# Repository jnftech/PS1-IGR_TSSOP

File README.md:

## Playstation 1 In-Game Reset (IGR)
### QSBs for One-wire Controller-PCB installs
<br/>
<br/>

These boards are variations on [PyroESP's](https://github.com/pyroesp) Playstation 1 Reset Mod project.

The original project and code can be found at https://github.com/pyroesp/PlayStation-1-Reset-Mod

To simplify the goal of this project: When installed into a Playstation 1 system, it facilitates a reset of the system using a button combination on controller 1, by tapping into the controller signals and toggling the system reset line. This is useful for those that have ODEs installed, as you can reset back to the menu of the ODE from the controller instead of getting up to hold the reset button down.

Originally I had posted a variation that was more or less a shrink of their original PCB (which used a SOIC package for the microcontroller), instead using the TSSOP version - to get the board as small as it could be for S&Gs and more of a "hardmode" install. This version of the project (while deprecated, unless you REALLY need to avoid installing to the controller PCB) is still hosted in the repository.

A while back (2002? Yes it has taken me that long to publish the final versions here) a member of the [Consolemods.org](https://www.consolemods.org) discord observed a variation on OSHpark that installed to the back of the controller PCB behind the player 1 port. However the project was not laid out correctly, thus the wrong (higher) voltage was applied to the microcontroller. This style of board is a "Quick Solder Board" (QSB), where the board is designed to sit on top of another PCB and solder directly to signal points (versus running a wire for each signal). Such a solution allows for a "one-wire" install of this project. All but one of the signals needed are available from the solder points of the controller ports themselves. The only wire that must be run is for the reset signal.
While these controller-PCB-mounted solutions were not uncommon at the time, the project on OSHpark appeared to the only published gerbers for folks that prefer to fabricate their own PCBs.
I decided to revisit the project to produce a correctly-wired version, using my own consoles for measurement. Some earlier versions of the gerbers were posted to the discord for members to use. This respository has three variations depending on your soldering preferences.
  
Code, details of the solution, original PCB design, and instructions for programming and installation are available at [pyroesp's Github](https://github.com/pyroesp). Programming-ready hex file in the [releases section](https://github.com/pyroesp/PlayStation-1-Reset-Mod/releases)

### Controller-port (Port 1) install, SOIC Package (Normal difficulty) [(OSHpark)](https://oshpark.com/shared_projects/fwJTyytg)

This variant more or less aimed to substitute the faulty one on OSHpark. Installs over the solder points for controller port 1 and uses the SOIC package of the microcontroller (MCU). This should be fairly easy to assemble for anyone with decent soldering skills.

### Controller-port (Port 1) install, TSSOP Package (Hard difficulty) [(OSHpark)](https://oshpark.com/shared_projects/G71d1amG)

This is almost identical to the above variant, and installs the exact same way. The only difference is the use of the TSSOP package for the MCU. This requires slightly tighter soldering skills.

### Controller-ribbon connector (Center of controller PCB) install, UQFN Package (Ultrahard difficulty) [(OSHpark)](https://oshpark.com/shared_projects/B2ZQAGCg)

Staying in the same spirit as my original visit to the project, this board aims to be as small is it can be. I realized that another spot on the controller PCB contained all the same signals as the controller port: The connector for the ribbon cable that connects the controller assembly to the main system board. This PCB installs to the back of that connector instead of the controller port. Continuing with that same spirit, I figured go all out and use the UQFN package of the MCU - which is the smallest package it comes in. However this means this board is significantly more difficult to assemble by hand. Not impossible - I hand assembled the one installed in my main console - but takes very good soldering skills and tools. I imagine this is the smallest "one-wire" install of this solution available. All that said, the actual installation of the board into the console should not be much more difficult than the other two options.

### BOM:

Only two components are needed:

**U1**<br/> Depending on which board you which to assemble, the part number for the MCU will differ slightly (only the last two characters of the part number matter in this case)
- SOIC: Microchip PIC16F18325-I/SL. [Digikey](https://www.digikey.com/en/products/detail/microchip-technology/PIC16F18325-I-SL/5323625)
- TSSOP: Microchip PIC16F18325-I/ST. [Digikey](https://www.digikey.com/en/products/detail/microchip-technology/PIC16F18325-I-ST/5323626)
- UQFN: Microchip PIC16F18325-I/JQ. [Digikey](https://www.digikey.com/en/products/detail/microchip-technology/PIC16F18325-I-JQ/5639473)

**C1**:<br/>You really don't need to be picky about this part. Any 100nf to 1000nf/1uf 0603-sized Ceramic capacitor rated at 16v or above will work. <br />
    Examples:<br />
        [Samsung CL10B104KB8NNNL](https://www.digikey.com/en/products/detail/samsung-electro-mechanics/CL10B104KB8NNNL/3894274)<br />
        [Murata GCJ188R71E104KA12D](https://www.digikey.com/en/products/detail/murata-electronics/GCJ188R71E104KA12D/7363221)

### Notes:
- These have not been designed with the PSone in mind, and are only tested on the original "phat" models. While the PSones have no good ODE option (where this mod is most useful), I may take a quick look the next time I have a PSone open (maybe requires another board revision). 
- There are other variants of the MCU you can use, depending on whether you have trouble sourcing the above (I did when I built my prototypes) but they may be a few cents more expensive as they have extra features or tolerances. In this project, they will all function identically:
  - The "I/" in the part number can be swapped with the "E/" variant. The latter is just "Extended Tempurature range"
  - This project uses the PIC16F18325 MCU, however the the PIC16F18**326** can also be used. It's the exact same MCU with a little bit more memory and storage. Same HEX file can be used to program either. The board I installed in my main console uses the PIC16F18326-E/JQ part. While the size of the code is fairly small, the next MCU down in the list (324) CANNOT be used as it lacks the dual SPI capability of the 325 and 326 (which this project requires).
- You will of course need a programmer to flash the code to the microcontroller, such as a PICkit3. This can be done in several ways:
  - The ICSP pads on board by soldering some temporary wiring to connect it to the programmer.
  - The ICSP pads by using a 2mm pitch pogo-pin PCB clamp such as this one on [Aliexpress](https://www.aliexpress.com/i/3256806664884457.html)
  - An alternative would be a DIP socket adapter ([an example of such on Aliexpress](https://www.aliexpress.com/item/32868905130.html)) to house the chip for programming before it is soldered to the board.
- The text in the bottom copper layer *may* cause some fabs to complain about the size of the text. OSHpark doesnt have an issue (they seem to fab whatever you throw at them, regardless if it comes out well in the final product), but I have experienced cases in the past where JLCPCB will remove any text from the board that they deem too small.

### Tools used for this project:
- Tracespace View (SVG conversions of gerbers for the above images) https://tracespace.io/view/
- KiCad 8.0.6 https://www.kicad.org/
- GIMP for some of the image edits.

### To-do
- Post more detailed installation instructions
- Post or link to reset line points for various motherboard revisions.

### License:
This derivative work maintains the same source license as the original board and project:  
Attribution-ShareAlike 4.0 International. See license file for more info

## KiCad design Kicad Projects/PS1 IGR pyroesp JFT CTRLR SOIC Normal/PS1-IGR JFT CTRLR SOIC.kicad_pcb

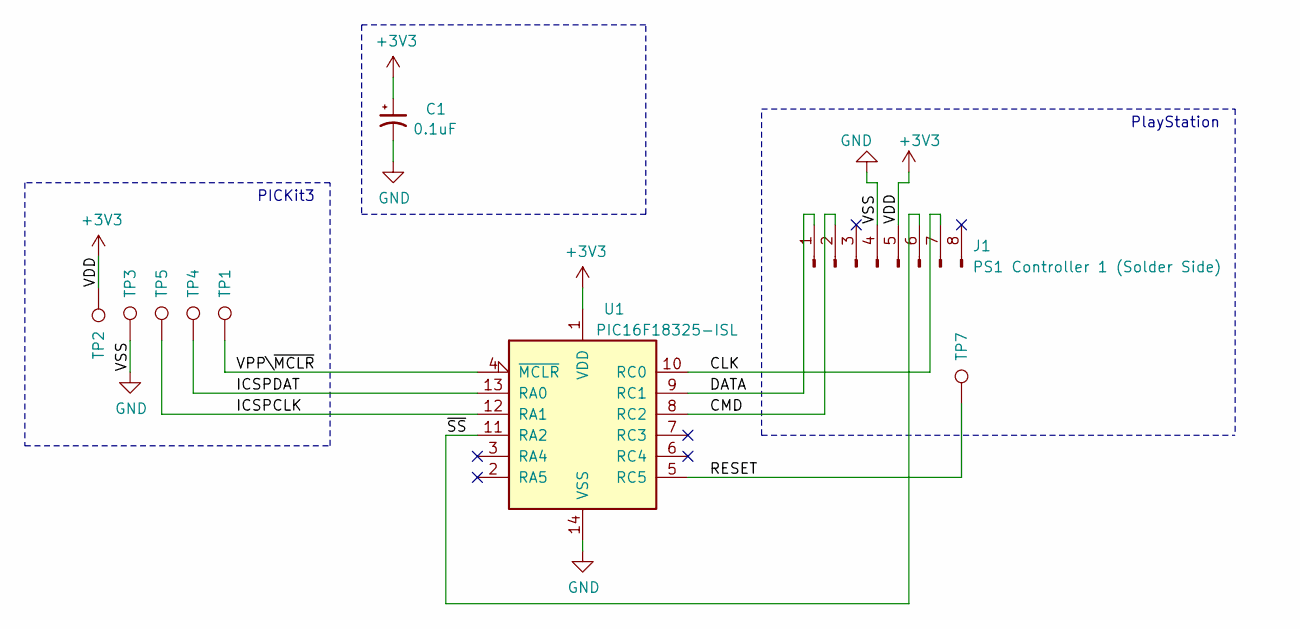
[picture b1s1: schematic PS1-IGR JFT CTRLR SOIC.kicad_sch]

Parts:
C1: 0.1uF; R_0603_0.8mm
J1: PS1 Controller 1 (Solder Side); PS1ControllerPort_SolderSide
TP1: VPP; TestPoint_Pad_NoSilk_D1.0mm
TP2: VDD; TestPoint_Pad_NoSilk_D1.0mm
TP3: VSS; TestPoint_Pad_NoSilk_D1.0mm
TP4: DAT; TestPoint_Pad_NoSilk_D1.0mm
TP5: CLK; TestPoint_Pad_NoSilk_D1.0mm
TP7: RST; Wirepad-2.54mm
U1: PIC16F18325-ISL; SOIC-14_3.9x8.7mm_Pitch1.27mm-JFT

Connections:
+3V3: C1.1, J1.5, TP2.1, U1.1 (VDD)
/CLK: J1.7, U1.10 (RC0)
/CMD: J1.2, U1.8 (RC2)
/DATA: J1.1, U1.9 (RC1)
/ICSPCLK: TP5.1, U1.12 (RA1)
/ICSPDAT: TP4.1, U1.13 (RA0)
/RESET: TP7.1, U1.5 (RC5)
/VPP\~MCLR: TP1.1, U1.4 (~MCLR)
/~SS: J1.6, U1.11 (RA2)
GND: C1.2, J1.4, TP3.1, U1.14 (VSS)

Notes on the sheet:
PICKit3
PlayStation

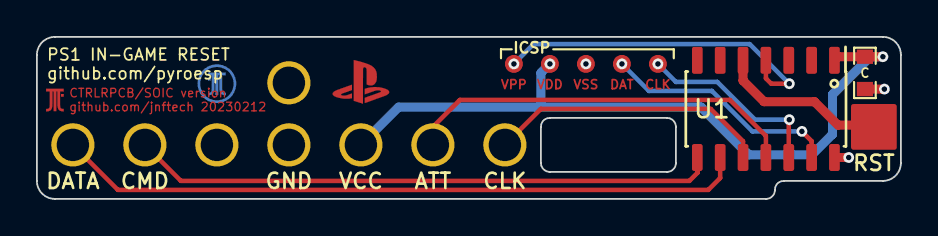
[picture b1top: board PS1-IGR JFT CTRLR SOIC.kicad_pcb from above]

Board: 2 copper layers, 48.0 x 9.0 mm, 9 parts (0 on the bottom side), 10 nets.

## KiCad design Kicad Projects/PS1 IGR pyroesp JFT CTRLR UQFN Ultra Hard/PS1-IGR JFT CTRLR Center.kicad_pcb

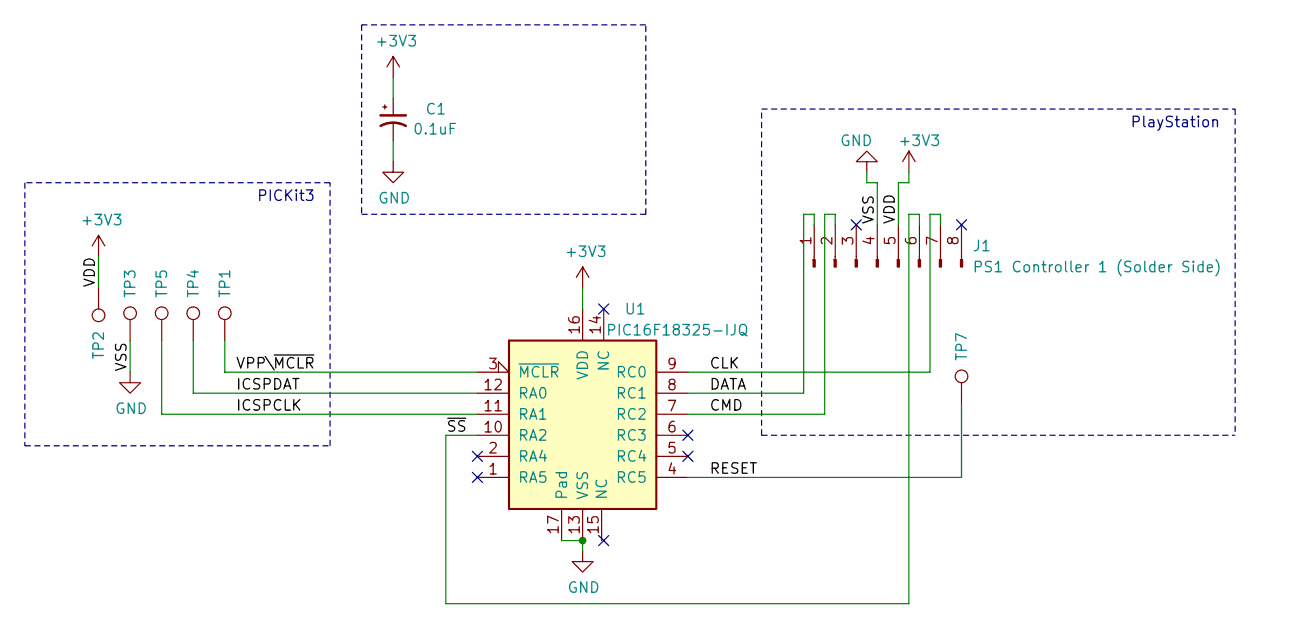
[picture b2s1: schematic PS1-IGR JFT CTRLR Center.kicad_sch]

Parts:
C1: 0.1uF; R_0603_0.8mm
J1: PS1 Controller 1 (Solder Side); PS1ctrlrRibbon_SolderSide_ForTHb
TP1: VPP; TestPoint_Pad_NoSilk_D1.0mm
TP2: VDD; TestPoint_Pad_NoSilk_D1.0mm
TP3: VSS; TestPoint_Pad_NoSilk_D1.0mm
TP4: DAT; TestPoint_Pad_NoSilk_D1.0mm
TP5: CLK; TestPoint_Pad_NoSilk_D1.0mm
TP7: RST; Wirepad-2x2.5mm
U1: PIC16F18325-IJQ; UQFN-16-1EP_4x4mm_P0.65mm_EP2.6x2.6mm

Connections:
+3V3: C1.1, J1.5, TP2.1, U1.16 (VDD)
/CLK: J1.7, U1.9 (RC0)
/CMD: J1.2, U1.7 (RC2)
/DATA: J1.1, U1.8 (RC1)
/ICSPCLK: TP5.1, U1.11 (RA1)
/ICSPDAT: TP4.1, U1.12 (RA0)
/RESET: TP7.1, U1.4 (RC5)
/VPP\~MCLR: TP1.1, U1.3 (~MCLR)
/~SS: J1.6, U1.10 (RA2)
GND: C1.2, J1.4, TP3.1, U1.13 (VSS), U1.17 (Pad)

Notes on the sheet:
PlayStation
PICKit3

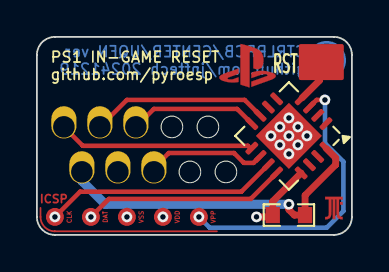
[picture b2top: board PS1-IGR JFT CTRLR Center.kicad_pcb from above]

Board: 2 copper layers, 17.5 x 11.0 mm, 9 parts (0 on the bottom side), 10 nets.

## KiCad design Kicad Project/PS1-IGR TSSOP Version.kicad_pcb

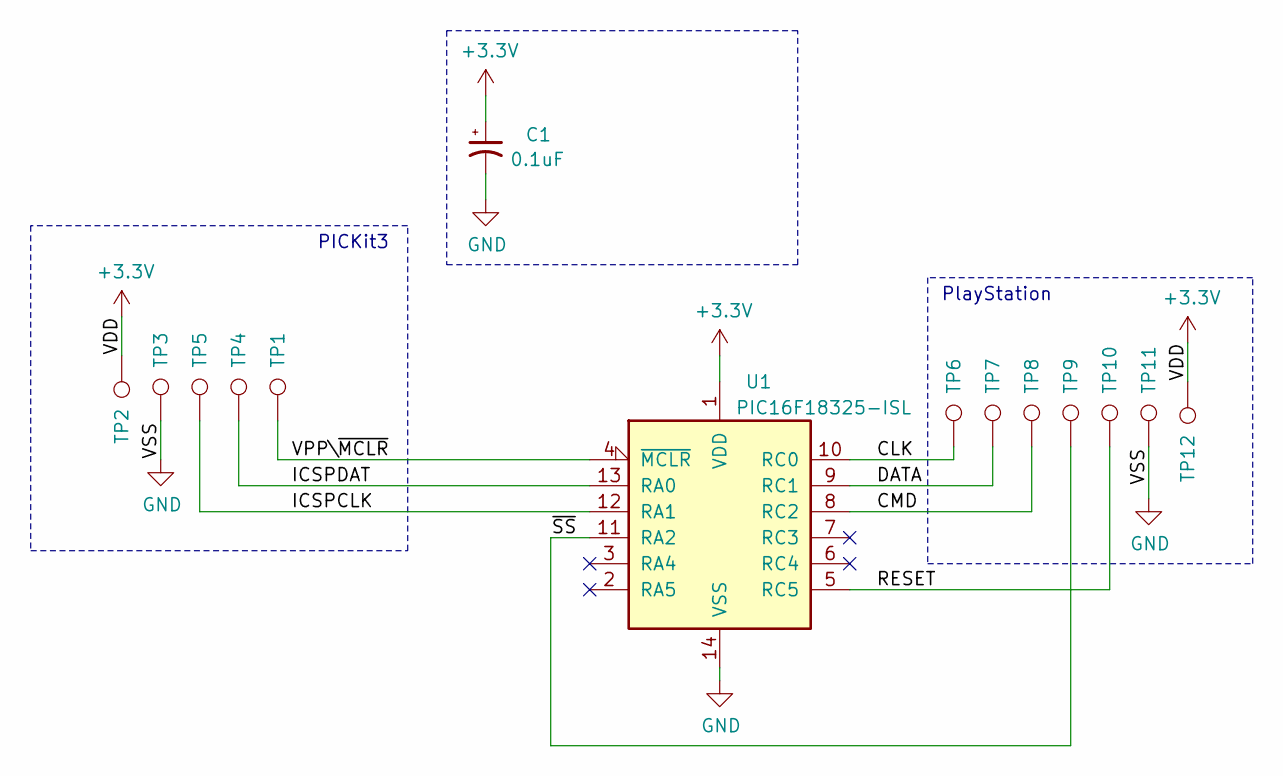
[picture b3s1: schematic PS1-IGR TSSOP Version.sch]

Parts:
C1: 0.1uF; R_0603_0.8mm
TP1: VPP; TestPoint_Pad_D1.0mm
TP2: VDD; TestPoint_Pad_D1.0mm
TP3: VSS; TestPoint_Pad_D1.0mm
TP4: DAT; TestPoint_Pad_D1.0mm
TP5: CLK; TestPoint_Pad_D1.0mm
TP6: CLK; Wirepad-1.2mm
TP7: DATA; Wirepad-1.2mm
TP8: CMD; Wirepad-1.2mm
TP9: ~SS; Wirepad-1.2mm
TP10: RST; Wirepad-1.2mm
TP11: VSS; Wirepad-1.2mm
TP12: 3V5; Wirepad-1.2mm
U1: PIC16F18325-ISL; TSSOP-14_4.4x5mm_Pitch0.65mm-JFT

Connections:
+3V3: C1.1, TP2.1, TP12.1, U1.1 (VDD)
/CLK: TP6.1, U1.10 (RC0)
/CMD: TP8.1, U1.8 (RC2)
/DATA: TP7.1, U1.9 (RC1)
/ICSPCLK: TP5.1, U1.12 (RA1)
/ICSPDAT: TP4.1, U1.13 (RA0)
/RESET: TP10.1, U1.5 (RC5)
/VPP\~MCLR: TP1.1, U1.4 (~MCLR)
/~SS: TP9.1, U1.11 (RA2)
GND: C1.2, TP3.1, TP11.1, U1.14 (VSS)

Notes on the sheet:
PICKit3
PlayStation

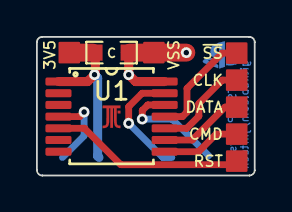
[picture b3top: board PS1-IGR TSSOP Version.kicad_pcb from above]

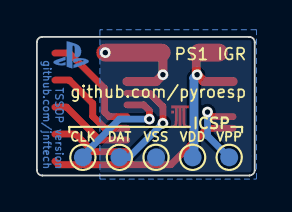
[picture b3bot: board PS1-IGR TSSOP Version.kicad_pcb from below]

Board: 2 copper layers, 12.1 x 7.7 mm, 14 parts (5 on the bottom side), 10 nets.

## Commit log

2021-11-08 Update README.md
    https://forum.kicad.info/t/warning-avoid-all-links-to-kicad-pcb-org-use-kicad-org/31521
2024-12-27 Rename PS1-IGR TSSOP Version (20210109).zip to PS1-IGR In-Console TSSOP Shrink Version (20210109).zip
    Rename file
2024-12-27 Rename PS1-IGR In-Console TSSOP Shrink Version (20210109).zip to PS1-IGR In-Console TSSOP Shrink Version (20210109 Old Deprecated).zip
2024-12-27 Delete Kicad Project directory
    Preparing for additional project files
2024-12-31 Update README.md
    Added OSHpark links
2024-12-31 Update README.md
    Cleaned up OSHpark links
